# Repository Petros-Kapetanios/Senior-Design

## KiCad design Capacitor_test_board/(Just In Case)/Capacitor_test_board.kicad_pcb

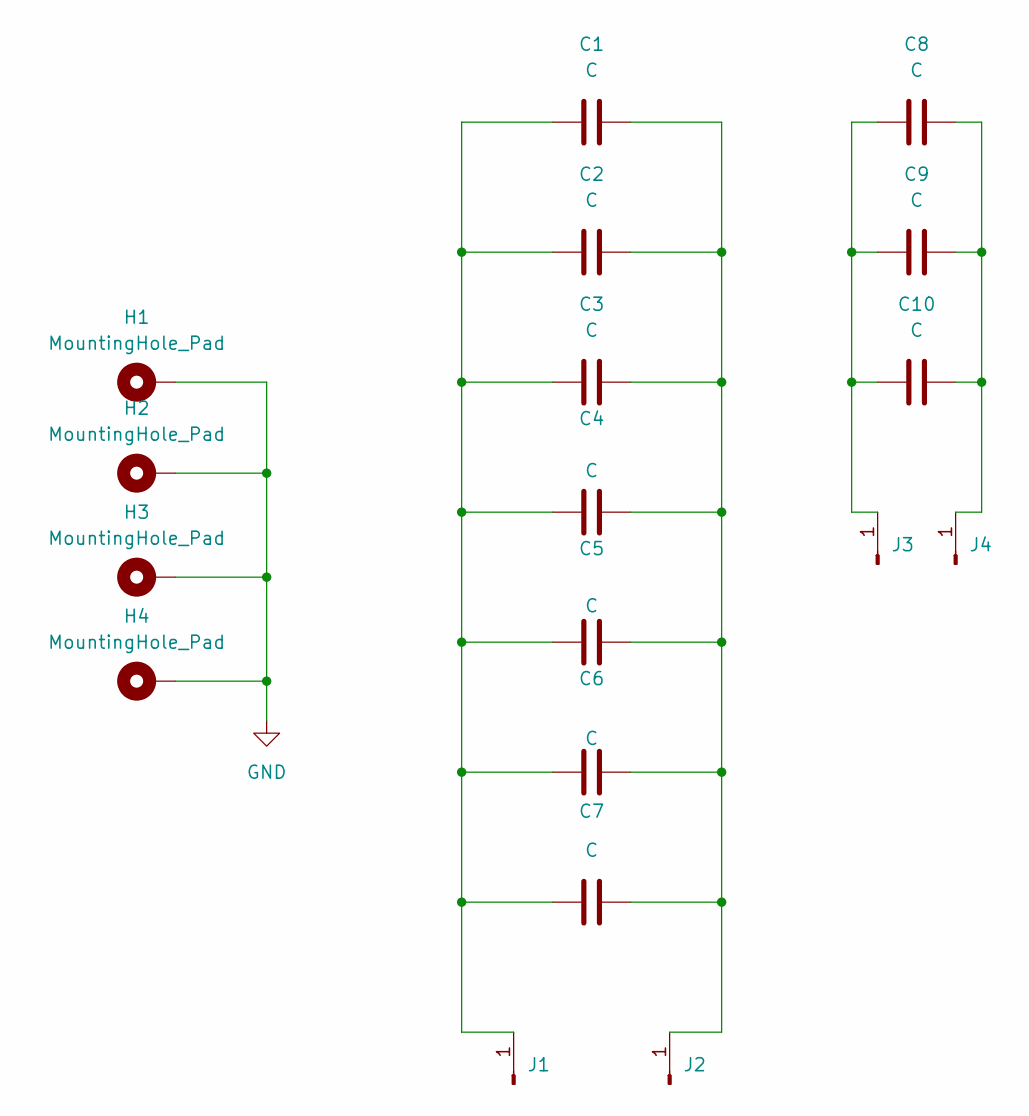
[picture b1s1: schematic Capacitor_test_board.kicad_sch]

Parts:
C1, C2, C3, C4, C5, C6, C7, C8, C9, C10: C; C_Rect_L24.0mm_W10.9mm_P22.50mm_MKT
H1, H2, H3, H4: MountingHole_Pad; MountingHole_3.2mm_M3_DIN965_Pad_TopBottom
J1, J2, J3, J4: Conn_01x01_Pin; SolderWire-2sqmm_1x01_D2mm_OD3.9mm

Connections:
GND: H1.1, H2.1, H3.1, H4.1
unnamed: C1.1, C2.1, C3.1, C4.1, C5.1, C6.1, C7.1, J1.1
unnamed: C1.2, C2.2, C3.2, C4.2, C5.2, C6.2, C7.2, J2.1
unnamed: C8.1, C9.1, C10.1, J3.1
unnamed: C8.2, C9.2, C10.2, J4.1

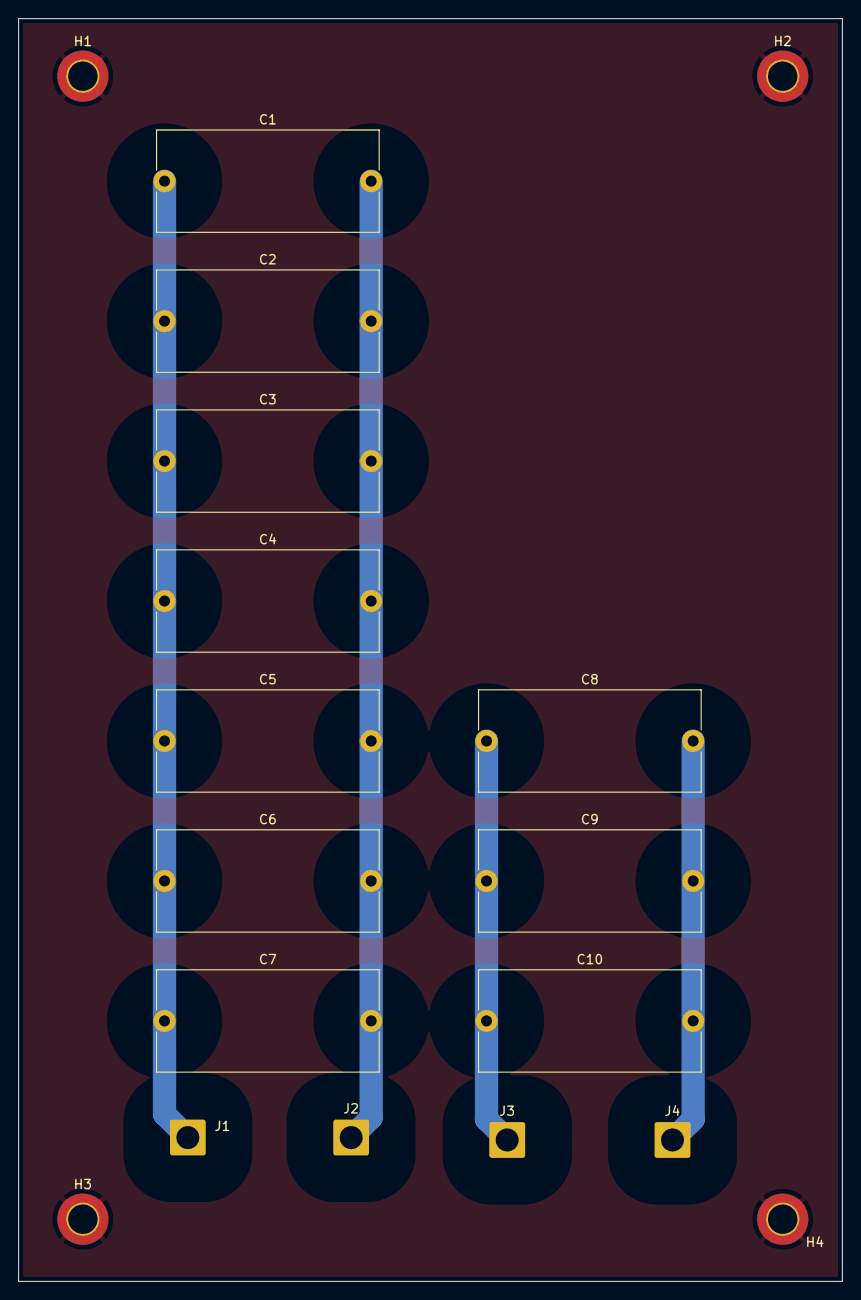
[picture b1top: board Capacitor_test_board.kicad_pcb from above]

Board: 2 copper layers, 89.7 x 137.5 mm, 18 parts (0 on the bottom side), 5 nets.

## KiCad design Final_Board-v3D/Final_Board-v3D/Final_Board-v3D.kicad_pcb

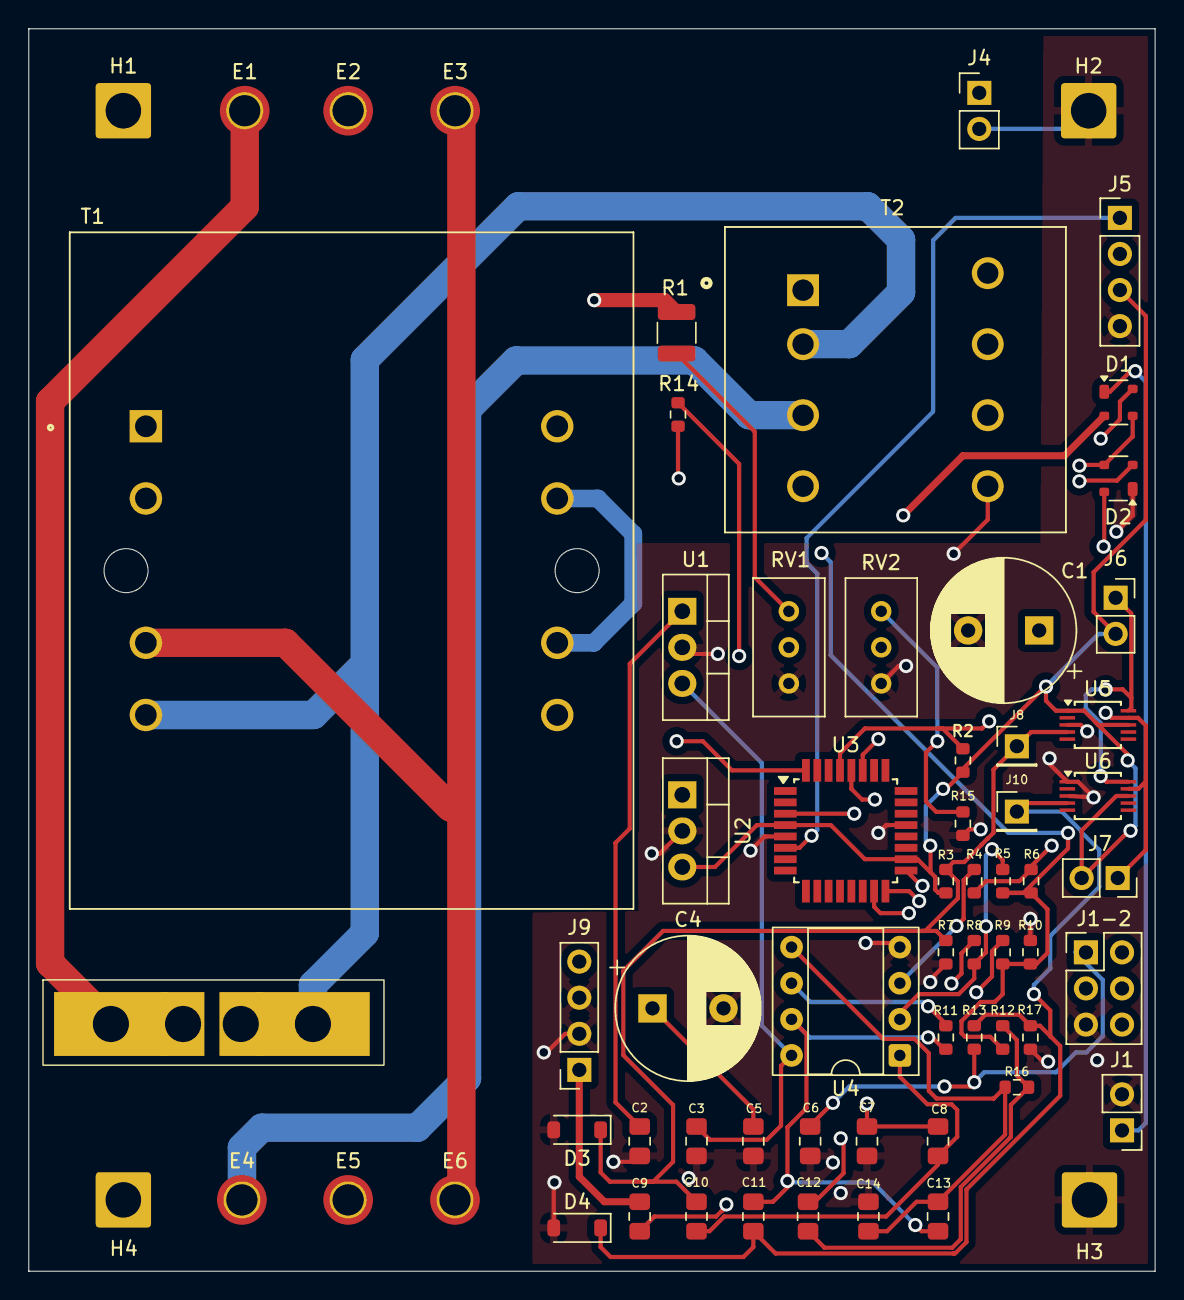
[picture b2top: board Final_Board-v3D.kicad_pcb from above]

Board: 4 copper layers, 79.3 x 87.5 mm, 65 parts (0 on the bottom side), 38 nets.

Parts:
C1, C4: 100 uF; CP_Radial_D10.0mm_P5.00mm
C2, C3, C5, C6: 1 uF; C_0805_2012Metric_Pad1.18x1.45mm_HandSolder
C7: 20 nF; C_0805_2012Metric_Pad1.18x1.45mm_HandSolder
C8, C13: 10 nF; C_0805_2012Metric_Pad1.18x1.45mm_HandSolder
C9, C10, C11, C12: 1.5 uF; C_0805_2012Metric_Pad1.18x1.45mm_HandSolder
C14: 22 nF; C_0805_2012Metric_Pad1.18x1.45mm_HandSolder
D1, D2: BAS3007; SOT-143
D3, D4: D_Zener; D_SOD-123
E1, E2, E3, E4, E5, E6: TestPoint_Small; MountingHole_2.2mm_M2_ISO7380_Pad_TopBottom
F1: Fuse; Fuseholder_Keystone_3555-2
H1, H2, H3, H4: Hole; SolderWire-2sqmm_1x01_D2mm_OD3.9mm
J1, J4: Conn_01x02_Pin; PinHeader_1x02_P2.54mm_Vertical
J1-2: Conn_02x03_Odd_Even; PinHeader_2x03_P2.54mm_Vertical
J5: Conn_01x04_Pin; PinHeader_1x04_P2.54mm_Vertical
J6, J7: Conn_01x02_Socket; PinSocket_1x02_P2.54mm_Vertical
J8, J10: Conn_01x01_Pin; PinHeader_1x01_P2.54mm_Vertical
J9: Conn_01x04_Socket; PinSocket_1x04_P2.54mm_Vertical
R1: 240 K; R_1210_3225Metric
R2, R3, R5, R7, R8, R11, R13, R14, R17: 10 K; R_0603_1608Metric
R4, R16: 20 K; R_0603_1608Metric
R6, R12: 51.1 K; R_0603_1608Metric
R9: 3 K; R_0603_1608Metric
R10: 1 K; R_0603_1608Metric
R15: 30; R_0603_1608Metric
RV1: 10K Pot; Potentiometer_Bourns_3296W_Vertical
RV2: 10 K Pot; Potentiometer_Bourns_3296W_Vertical
T1: VPP12-800; XFMR_VPP12-800
T2: CSE185L; XFMR_CSE185L
U1: 12 V Regulator; TO-220-3_Vertical
U2: 5 V Regulator; TO-220-3_Vertical
U3: ATmega328PB-A; TQFP-32_7x7mm_P0.8mm
U4: LM358; DIP-8_W7.62mm_Socket
U5, U6: ADS1115IDGS; TSSOP-10_3x3mm_P0.5mm

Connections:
5v: C6.1, J1-2.2, J5.3, J6.2, J7.2, R2.1, R3.1, R13.1, U2.3 (VO), U3.4 (VCC), U3.18 (AVCC), U5.1 (ADDR), U5.8 (VDD), U6.8 (VDD)
GND: C1.2, C2.2, C3.2, C4.2, C5.2, C6.2, C7.2, C14.1, D2.1 (-), D3.2 (A), D4.2 (A), E2.1, E5.1, H1.1, H2.1, H3.1, J1.2, J1-2.6, J4.2, J5.4, J9.2, J9.3, R7.2, R10.2, R15.1, R17.2, RV1.3, RV2.3, T1.1, T2.5, U1.2 (GND), U2.2 (GND), U3.5 (GND), U3.21 (GND), U4.4 (V-), U5.3 (GND), U6.1 (ADDR), U6.3 (GND)
unnamed: C9.2, R4.1, R6.2
unnamed: C8.2, C10.1, R8.2, U4.1
unnamed: C11.1, C13.2, R11.2, U4.7
unnamed: C12.1, RV2.2
unnamed: C12.2, R12.2, R16.1
unnamed: C1.1, C2.1, D1.4 (+), U1.1 (VI)
unnamed: D1.1 (-), J1.1
unnamed: D1.2, T1.12
unnamed: D1.3, D2.3, T1.7
unnamed: C4.1, C5.1, D2.4 (+), U2.1 (VI)
unnamed: D2.2, T1.9, T1.10
unnamed: C10.2, D3.1 (K), J8.1, R3.2, R7.1, U5.4 (AIN0)
unnamed: C11.2, D4.1 (K), J10.1, R13.2, R17.1, U6.4 (AIN0)
unnamed: F1.2, T1.6, T2.2
unnamed: J1-2.1, U3.16 (PB4)
unnamed: J1-2.3, U3.17 (PB5)
unnamed: J1-2.4, U3.15 (PB3)
unnamed: J1-2.5, R2.2, U3.29 (~RESET/PC6)
unnamed: J4.1, U3.32 (PD2)
unnamed: J5.1, U3.6 (PE1)
unnamed: J6.1, U3.28 (PC5), U5.10 (SCL), U6.10 (SCL)
unnamed: J7.1, U3.27 (PC4), U5.9 (SDA), U6.9 (SDA)
unnamed: C9.1, J9.1, RV1.2
unnamed: E1.1, F1.1
unnamed: E3.1, E6.1, T1.4
unnamed: E4.1, T2.3
unnamed: R1.1, RV1.1
unnamed: R1.2, T1.3
unnamed: R5.1, R6.1, R9.2, R10.1, R12.1, R14.2
unnamed: R15.2, RV2.1, T2.8
unnamed: C7.1, C8.1, R4.2, U4.3 (+)
unnamed: R5.2, R8.1, U4.2 (-)
unnamed: C13.1, C14.2, R16.2, U4.5 (+)
unnamed: R11.1, R14.1, U4.6 (-)
SDA: J5.2, U3.3 (PE0)
VCC: C3.1, R9.1, U1.3 (VO), U4.8 (V+)
